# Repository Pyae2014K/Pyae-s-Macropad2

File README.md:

# Pyae-s-Macropad2

My macropad is a 13 key macropad with a rotary encoder and per-key RGB.
It uses QMK firmware

It serves as a macropad that I can use every day to be more productive.

## Features:
- EC11 Rotary encoder for volume
- 13 keys, 12 for macros and 1 for swapping layers
- Per-key RGB
- [VIA](https://www.caniusevia.com/) support

## PCB:
My PCB was made using Kicad.

Schematic

PCB

I used [Joe Scotto's](https://www.youtube.com/@joe_scotto) footprints for most of my footprints.

## CAD Model
Everything fits together perfectly using just 4 M3 Bolts and heat-set inserts.

It has 4 different pieces, Top Case, Bottom Case, Plate, and a Rotary Encoder Knob

This model was made using Shapr 3D.

## Firmware
This macropad uses [QMK](https://qmk.fm/) firmware for its code.
- 13 keys; 12 for macros, 1 for layers
- Rotary encoder used to change volume
- Per-key LEDs

## BOM:
Here is everything that is needed to make this macropad
| Qty | Part | Description |
|-----:|------|-------------|
| 1 | Custom PCB | 5x3 Macropad board |
| 1 | Seeed XIAO RP2040 | Microcontroller |
| 13 | MX-Style Switches | Mechanical keyboard switch |
| 13 | DSA Keycaps | DSA profile keycap |
| 14 | 1N4148 Diodes | DO-35 through-hole diode |
| 1 | EC11E Rotary Encoder | Rotary encoder |
| 4 | M3x16mm Screws | M3 screw |
| 4 | M3x5x4mm Heatset Inserts | M3 threaded heat-set insert |
| 13 | SK6812 MINI-E LEDs | LEDs |
| 1 | Case Top | 3D printed top case |
| 1 | Case Bottom | 3D printed bottom case |
| 1 | Plate | Switch plate |
| 1 | Knob | Rotary encoder knob |

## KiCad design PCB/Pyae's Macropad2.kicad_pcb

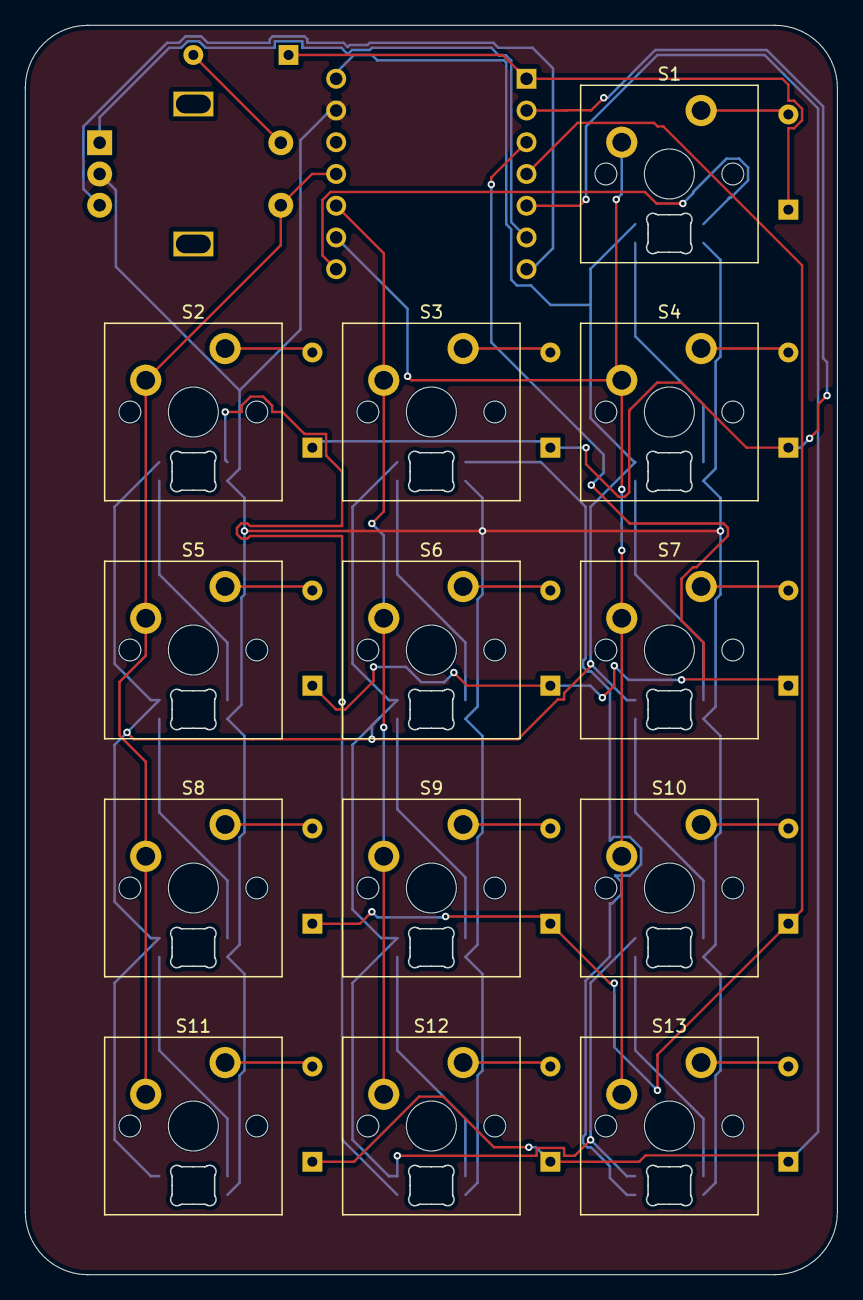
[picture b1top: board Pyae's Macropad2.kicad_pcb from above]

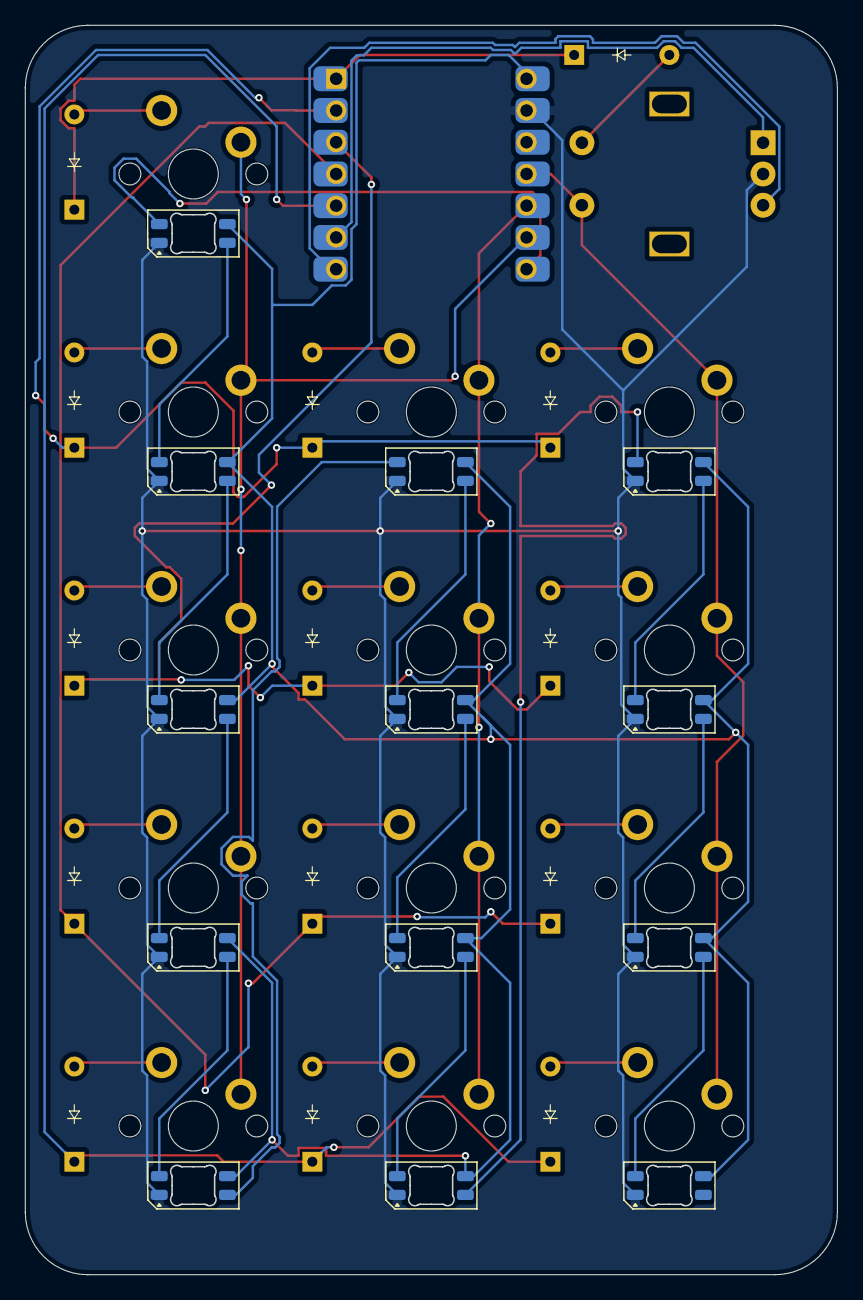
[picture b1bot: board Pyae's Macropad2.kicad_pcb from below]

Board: 2 copper layers, 65.0 x 100.0 mm, 42 parts (28 on the bottom side), 39 nets.

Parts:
D1, D2, D3, D4, D5, D6, D7, D8, D9, D10, D11, D12, D13, D14: Diode_DO-35
D15, D16, D17, D18, D19, D20, D21, D22, D23, D24, D25, D26, D27: SK6812MINI-E; LED_SK6812MINI-E_3.2x2.8mm_P1.5mm_ReverseMount
S1, S2, S3, S4, S5, S6, S7, S8, S9, S10, S11, S12, S13: MX_PCB_1.00u
SW1: RotaryEncoder_Switch; Encoder_EC11_MX
U1: MOUDLE-SEEEDUINO-XIAO; Seeed_XIAO_RP2040

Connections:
A: SW1.A, U1.6 (PA9_A5_D5_SCL)
B: SW1.B, U1.7 (PB08_A6_D6_TX)
Col0: S2.1, S5.1, S8.1, S11.1, SW1.S1, U1.11 (PA6_A10_D10_MOSI)
Col1: S3.1, S6.1, S9.1, S12.1, U1.10 (PA5_A9_D9_MISO)
Col2: S1.1, S4.1, S7.1, S10.1, S13.1, U1.9 (PA7_A8_D8_SCK)
GND: D15.1 (VSS), D16.1 (VSS), D17.1 (VSS), D18.1 (VSS), D19.1 (VSS), D20.1 (VSS), D21.1 (VSS), D22.1 (VSS), D23.1 (VSS), D24.1 (VSS), D25.1 (VSS), D26.1 (VSS), D27.1 (VSS), SW1.C, U1.13 (GND)
LED: D15.2 (DIN), U1.8 (PB09_A7_D7_RX)
unnamed: D1.2 (A), S1.2
unnamed: D2.2 (A), S2.2
unnamed: D3.2 (A), S3.2
unnamed: D4.2 (A), S4.2
unnamed: D5.2 (A), S5.2
unnamed: D6.2 (A), S6.2
unnamed: D7.2 (A), S7.2
unnamed: D8.2 (A), S8.2
unnamed: D9.2 (A), S9.2
unnamed: D10.2 (A), S10.2
unnamed: D11.2 (A), S11.2
unnamed: D12.2 (A), S12.2
unnamed: D13.2 (A), S13.2
unnamed: D15.4 (DOUT), D16.2 (DIN)
unnamed: D16.4 (DOUT), D17.2 (DIN)
unnamed: D17.4 (DOUT), D18.2 (DIN)
unnamed: D18.4 (DOUT), D19.2 (DIN)
unnamed: D19.4 (DOUT), D20.2 (DIN)
unnamed: D20.4 (DOUT), D21.2 (DIN)
unnamed: D21.4 (DOUT), D22.2 (DIN)
unnamed: D22.4 (DOUT), D23.2 (DIN)
unnamed: D23.4 (DOUT), D24.2 (DIN)
unnamed: D24.4 (DOUT), D25.2 (DIN)
unnamed: D25.4 (DOUT), D26.2 (DIN)
unnamed: D26.4 (DOUT), D27.2 (DIN)
Row0: D1.1 (K), D14.1 (K), U1.1 (PA02_A0_D0)
Row1: D2.1 (K), D3.1 (K), D4.1 (K), U1.2 (PA4_A1_D1)
Row2: D5.1 (K), D6.1 (K), D7.1 (K), U1.3 (PA10_A2_D2)
Row3: D8.1 (K), D9.1 (K), D10.1 (K), U1.4 (PA11_A3_D3)
Row4: D11.1 (K), D12.1 (K), D13.1 (K), U1.5 (PA8_A4_D4_SDA)
S2: D14.2 (A), SW1.S2
VCC: D15.3 (VDD), D16.3 (VDD), D17.3 (VDD), D18.3 (VDD), D19.3 (VDD), D20.3 (VDD), D21.3 (VDD), D22.3 (VDD), D23.3 (VDD), D24.3 (VDD), D25.3 (VDD), D26.3 (VDD), D27.3 (VDD), U1.14 (5V)
